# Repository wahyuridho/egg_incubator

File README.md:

# egg_incubator

Hai ini adalah projek penetas telur yang saya buat, yang mana bertujuan untuk membuat sebuah alat yang dapat digunakan untuk menetaskan telur dari burung puyuh
alat & bahan
1. Arduino pro mini / arduino nano (sesuaikan dengan design PCB)
2. DS18B20
3. LCD 16x2
4. Relay
5. 3 Buah Push Button
6. Optocoupler PC817
7. Resistor 4k7, 470, 120
8. Transistor 2N3905 or ..
9. Diode 1N4007 or ...
10. Jack DC barrel
11. Capacitor 47uF, 10uF, 0.1uF
12. IC L7805

Anda bisa melihat untuk komponen yang digunakan dengan melihat tampilan 3D dari Kicad

note : untuk komponen yang tidak muncul 3D design nya bisa dicari pada folder 3D Model

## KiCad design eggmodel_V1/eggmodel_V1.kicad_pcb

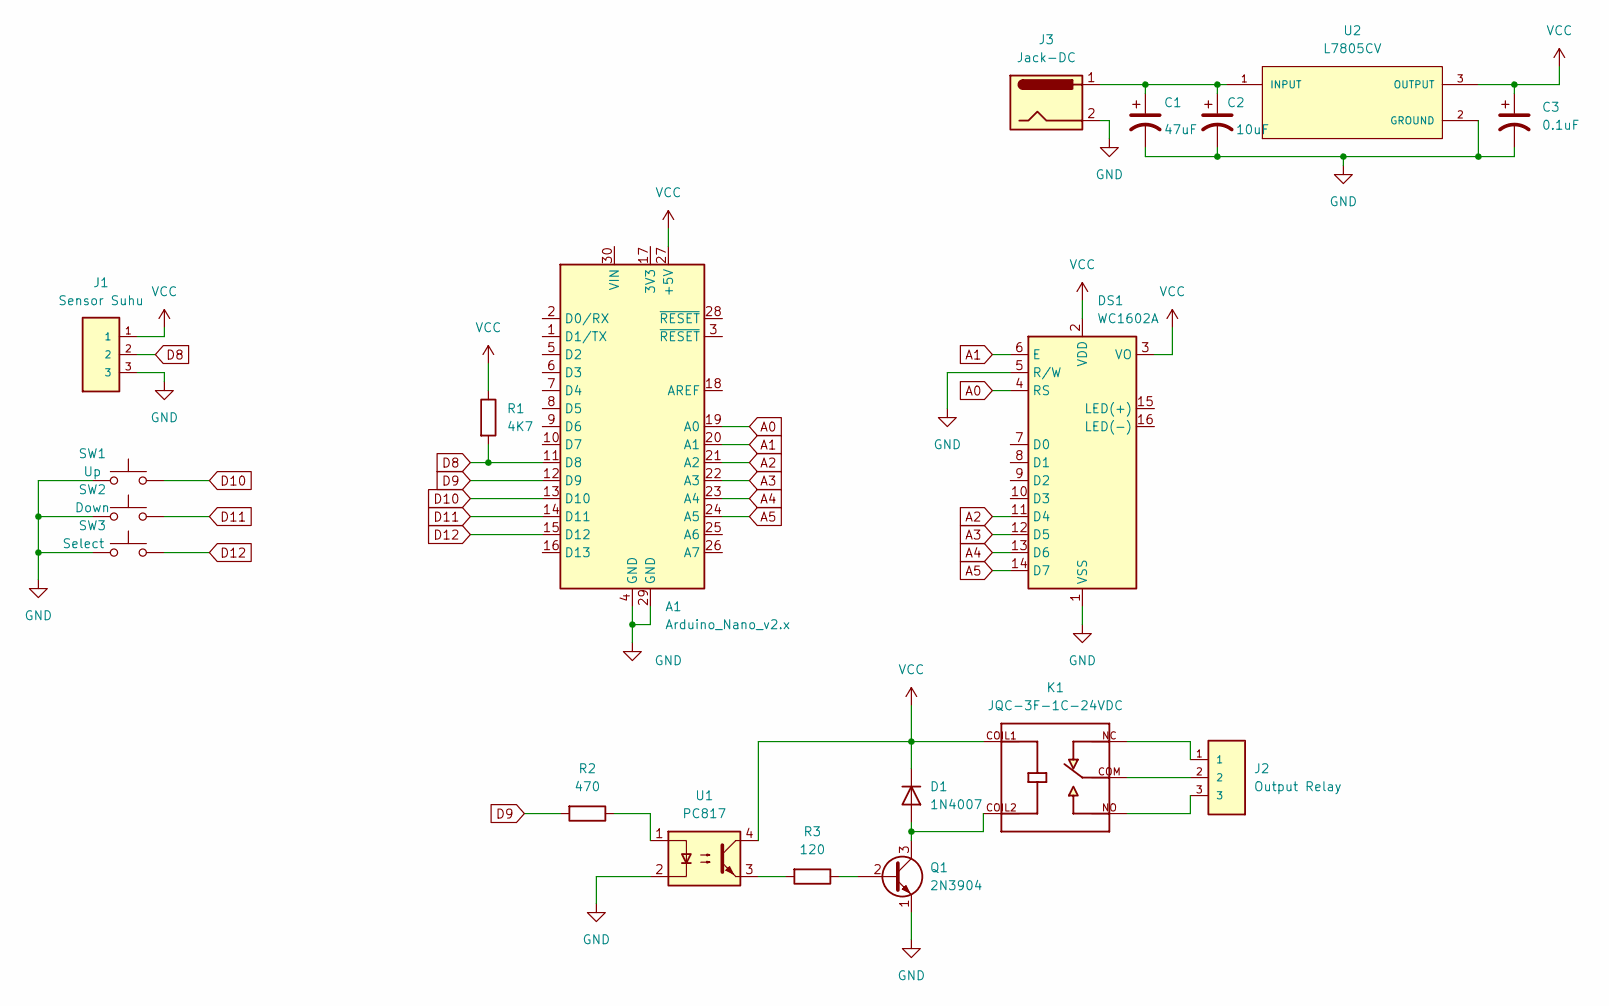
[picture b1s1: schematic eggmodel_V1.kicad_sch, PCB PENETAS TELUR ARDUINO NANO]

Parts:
A1: Arduino_Nano_v2.x; Arduino_Nano
C1: 47uF; CP_Radial_D6.3mm_P2.50mm
C2: 10uF; CP_Radial_D6.3mm_P2.50mm
C3: 0.1uF; CP_Radial_D6.3mm_P2.50mm
D1: 1N4007; D_DO-41_SOD81_P10.16mm_Horizontal
DS1: WC1602A
J1: Sensor Suhu; TE_282834-3
J2: Output Relay; TE_282834-3
J3: Jack-DC; BarrelJack_Horizontal
K1: JQC-3F-1C-24VDC; RELAY_JQC-3F-1C-24VDC; PARTREV N/A
Q1: 2N3904; TO-92_Wide
R1: 4K7; R_Axial_DIN0204_L3.6mm_D1.6mm_P7.62mm_Horizontal
R2: 470; R_Axial_DIN0204_L3.6mm_D1.6mm_P7.62mm_Horizontal
R3: 120; R_Axial_DIN0204_L3.6mm_D1.6mm_P7.62mm_Horizontal
SW1: Up; SW_PUSH_6mm
SW2: Down; SW_PUSH_6mm
SW3: Select; SW_PUSH_6mm
U1: PC817; DIP-4_W7.62mm
U2: L7805CV; TO255P1040X460X1968-3; PARTREV 36

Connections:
A0: A1.19 (A0), DS1.4 (RS)
A1: A1.20 (A1), DS1.6 (E)
A2: A1.21 (A2), DS1.11 (D4)
A3: A1.22 (A3), DS1.12 (D5)
A4: A1.23 (A4), DS1.13 (D6)
A5: A1.24 (A5), DS1.14 (D7)
D8: A1.11 (D8), J1.2, R1.2
D9: A1.12 (D9), R2.2
D10: A1.13 (D10), SW1.2
D11: A1.14 (D11), SW2.2
D12: A1.15 (D12), SW3.2
GND: A1.4 (GND), A1.29 (GND), C1.2, C2.2, C3.2, DS1.1 (VSS), DS1.5 (R/W), J1.3, J3.2, Q1.1 (E), SW1.1, SW2.1, SW3.1, U1.2, U2.2 (GROUND)
unnamed: C1.1, C2.1, J3.1, U2.1 (INPUT)
unnamed: D1.2 (A), K1.COIL2, Q1.3 (C)
unnamed: J2.1, K1.NC
unnamed: J2.2, K1.COM
unnamed: J2.3, K1.NO
unnamed: Q1.2 (B), R3.1
unnamed: R2.1, U1.1
unnamed: R3.2, U1.3
VCC: A1.27 (+5V), C3.1, D1.1 (K), DS1.2 (VDD), DS1.3 (VO), J1.1, K1.COIL1, R1.1, U1.4, U2.3 (OUTPUT)

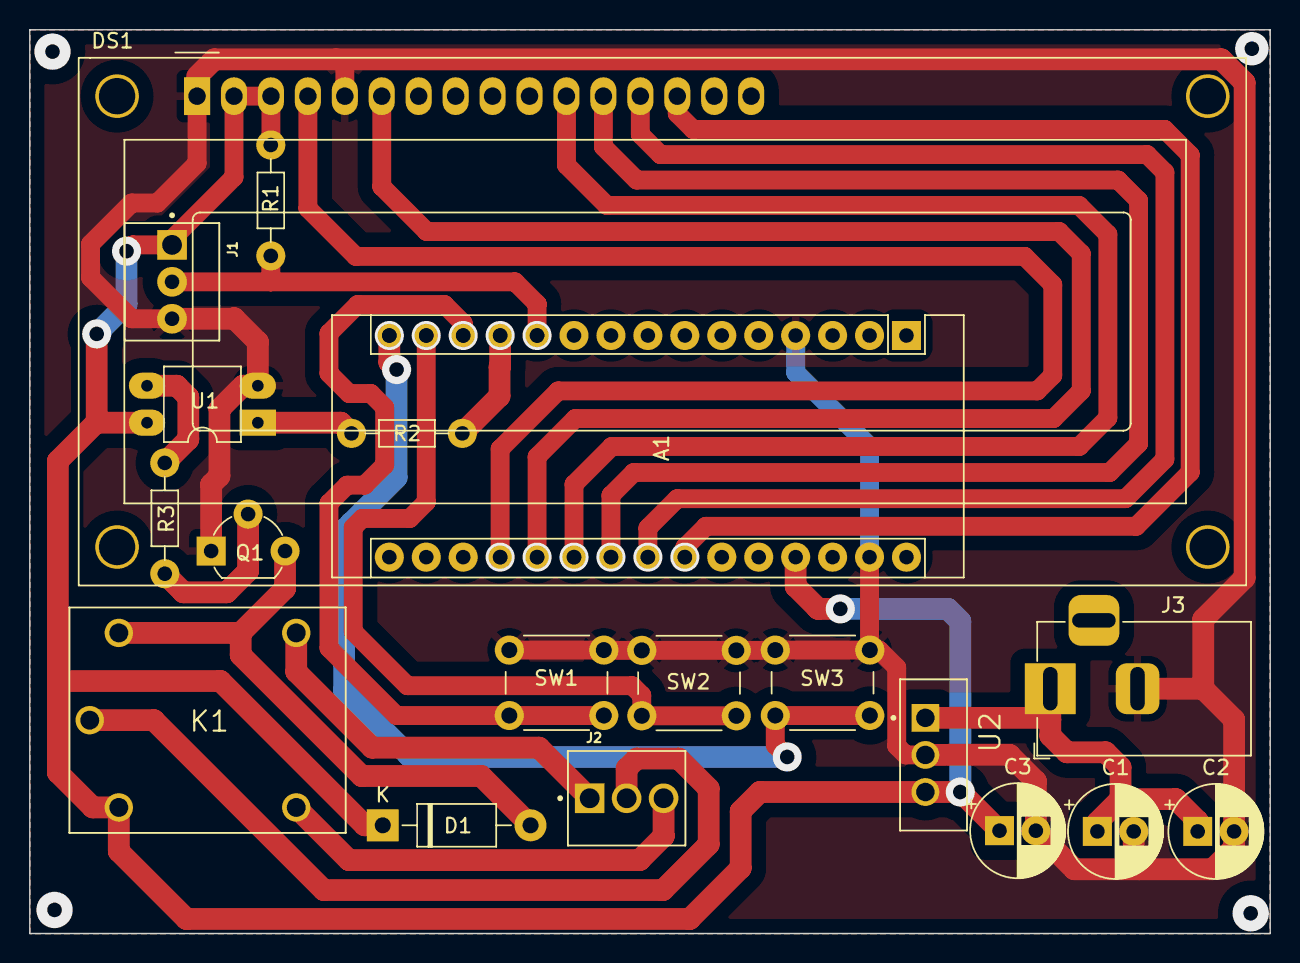
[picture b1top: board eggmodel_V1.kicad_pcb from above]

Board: 2 copper layers, 85.3 x 62.1 mm, 19 parts (0 on the bottom side), 21 nets.

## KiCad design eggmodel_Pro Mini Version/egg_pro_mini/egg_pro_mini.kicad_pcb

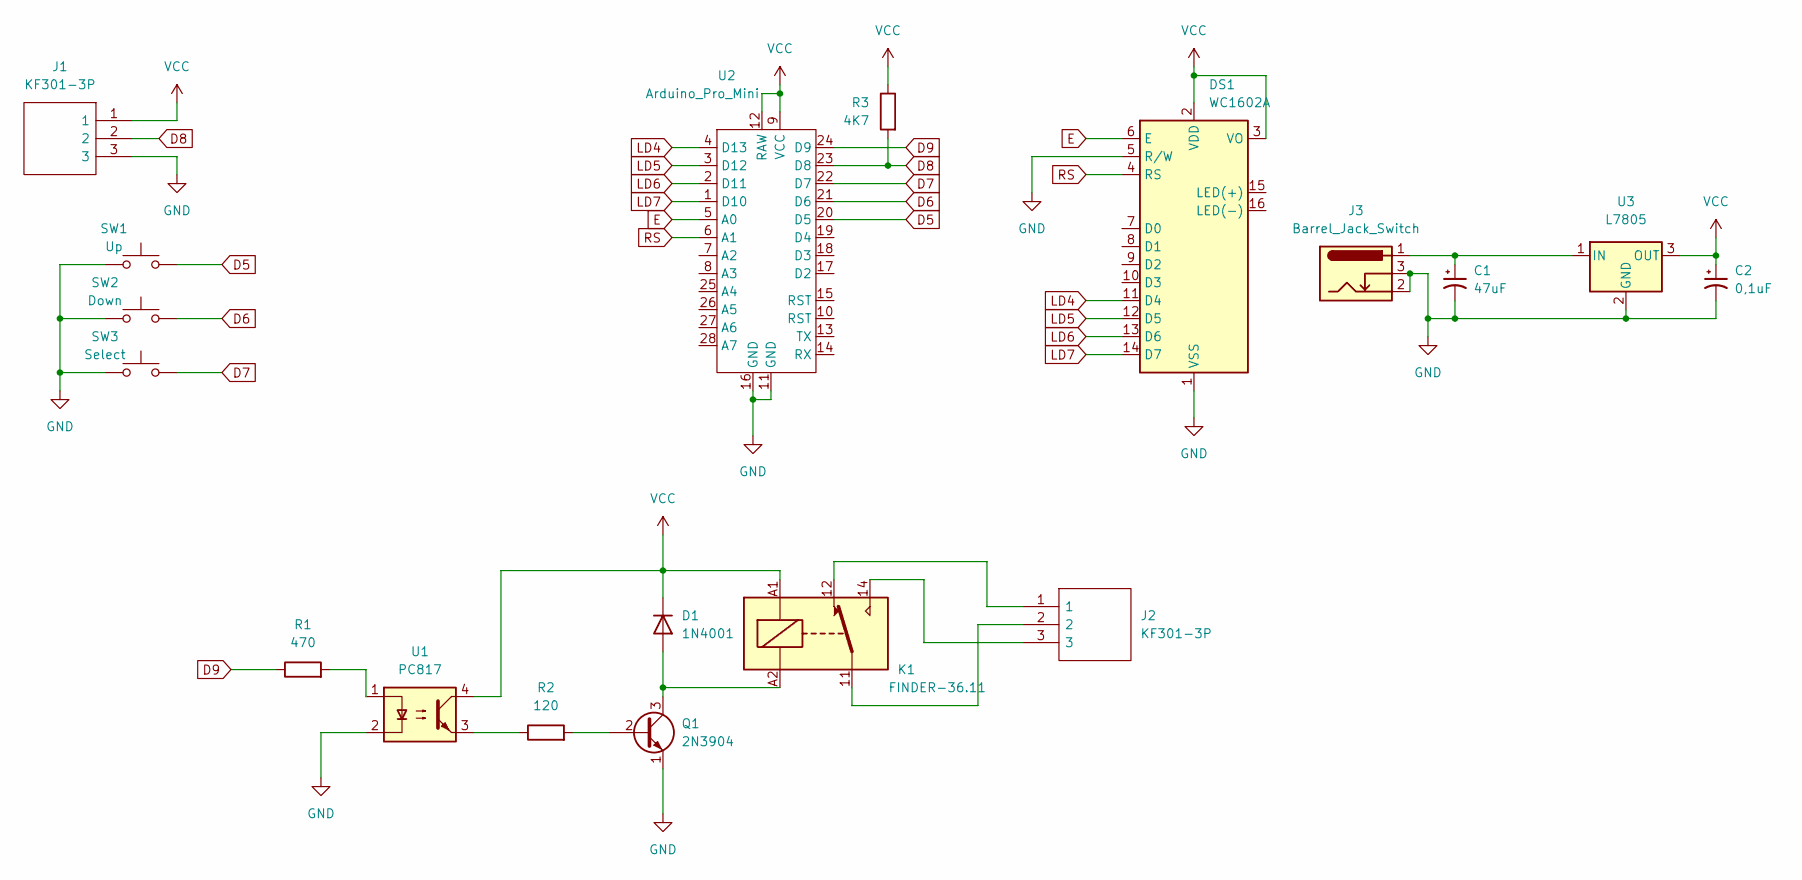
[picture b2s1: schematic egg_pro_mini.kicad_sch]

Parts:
C1: 47uF; CP_Radial_D5.0mm_P2.50mm
C2: 0,1uF; CP_Radial_D5.0mm_P2.50mm
D1: 1N4001; D_DO-41_SOD81_P10.16mm_Horizontal
DS1: WC1602A
J1, J2: KF301-3P; KF3013P; Manufacturer_Part_Number KF301-3P
J3: Barrel_Jack_Switch; BarrelJack_Horizontal
K1: FINDER-36.11; Relay_SPDT_Finder_36.11
Q1: 2N3904; TO-92_Wide
R1: 470; R_Axial_DIN0204_L3.6mm_D1.6mm_P7.62mm_Horizontal
R2: 120; R_Axial_DIN0204_L3.6mm_D1.6mm_P7.62mm_Horizontal
R3: 4K7; R_Axial_DIN0204_L3.6mm_D1.6mm_P7.62mm_Horizontal
SW1: Up; SW_PUSH_6mm_H8.5mm
SW2: Down; SW_PUSH_6mm_H8.5mm
SW3: Select; SW_PUSH_6mm_H8.5mm
U1: PC817; DIP-4_W7.62mm
U2: Arduino_Pro_Mini; arduino_pro_mini_mega168
U3: L7805; TO255P1040X460X1968-3

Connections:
D5: SW1.2, U2.20 (D5)
D6: SW2.2, U2.21 (D6)
D7: SW3.2, U2.22 (D7)
D8: J1.2, R3.2, U2.23 (D8)
D9: R1.1, U2.24 (D9)
E: DS1.6 (E), U2.5 (A0)
GND: C1.2, C2.2, DS1.1 (VSS), DS1.5 (R/W), J1.3, J3.2, J3.3, Q1.1 (E), SW1.1, SW2.1, SW3.1, U1.2, U2.11 (GND), U2.16 (GND), U3.2 (GND); also elsewhere on the board
LD4: DS1.11 (D4), U2.4 (D13)
LD5: DS1.12 (D5), U2.3 (D12)
LD6: DS1.13 (D6), U2.2 (D11)
LD7: DS1.14 (D7), U2.1 (D10)
unnamed: C1.1, J3.1, U3.1 (IN)
unnamed: D1.2 (A), K1.A2, Q1.3 (C)
unnamed: J2.1, K1.12
unnamed: J2.2, K1.11
unnamed: J2.3, K1.14
unnamed: Q1.2 (B), R2.2
unnamed: R1.2, U1.1
unnamed: R2.1, U1.3
RS: DS1.4 (RS), U2.6 (A1)
VCC: C2.1, D1.1 (K), DS1.2 (VDD), DS1.3 (VO), J1.1, K1.A1, R3.1, U1.4, U2.9 (VCC), U2.12 (RAW), U3.3 (OUT); also elsewhere on the board

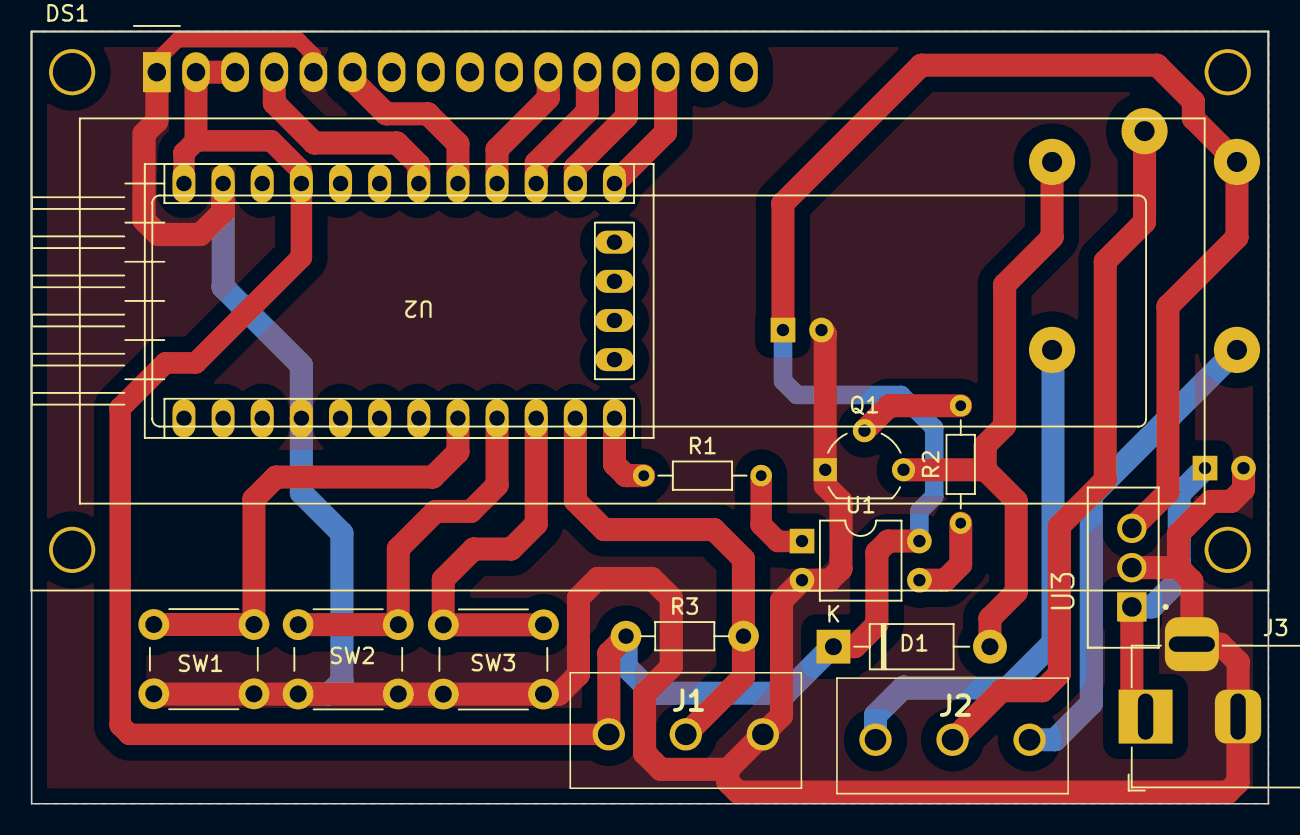
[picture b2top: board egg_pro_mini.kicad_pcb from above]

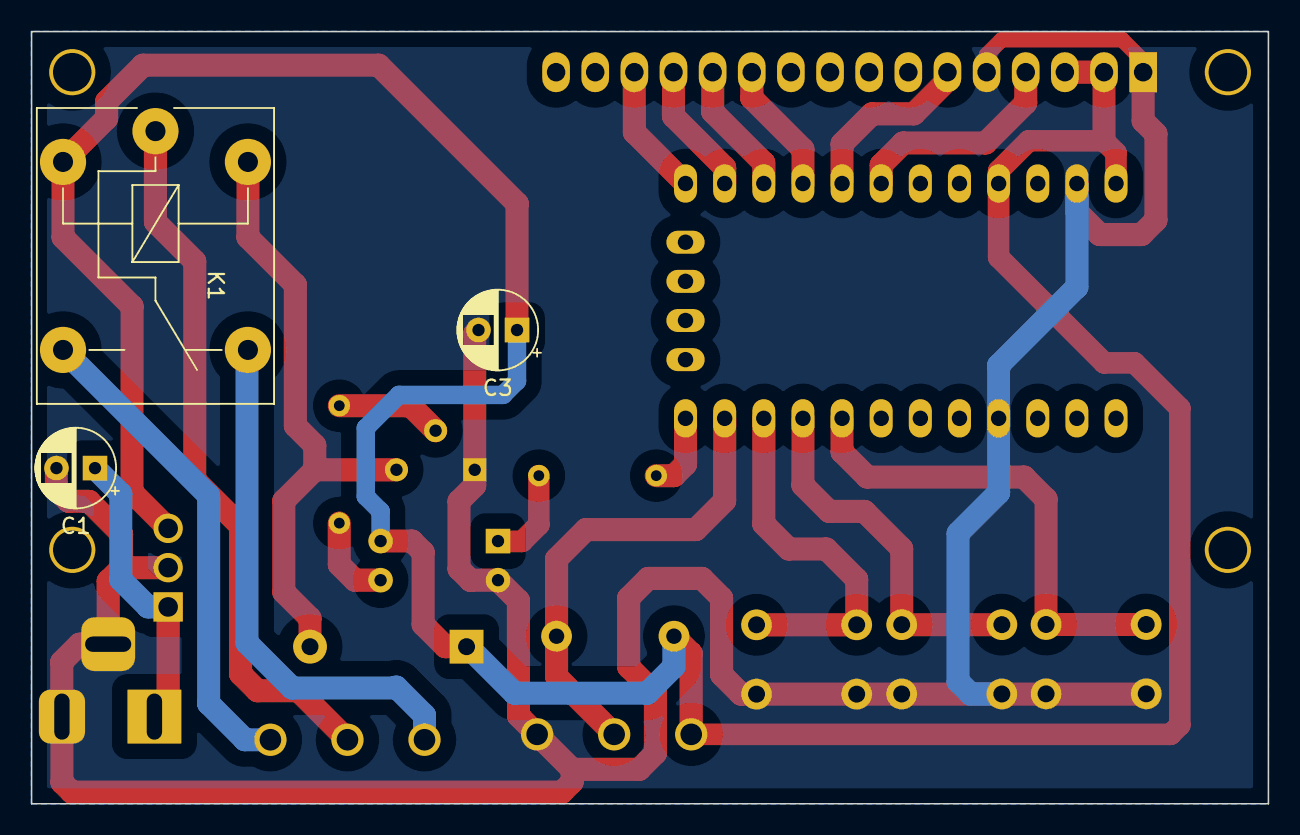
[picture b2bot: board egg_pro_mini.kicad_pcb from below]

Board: 2 copper layers, 80.3 x 50.1 mm, 18 parts (3 on the bottom side), 21 nets.

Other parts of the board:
C3: 0,1uF; CP_Radial_D5.0mm_P2.50mm

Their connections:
GND: C3.2; also elsewhere on the board
VCC: C3.1; also elsewhere on the board

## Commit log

2022-02-05 Versi awal
